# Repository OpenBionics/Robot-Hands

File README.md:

# Overview

OpenBionics is an initiative for the development of:
* open source
* affordable
* light-weight
* modular

robot hands and myoelectric prosthetic devices, that can be easily reproduced using off-the-shelf materials.

This repository contains all the necessary files, to replicate our robot hands.

For more information visit [OpenBionics.](http://www.openbionics.org/)

We have published a complete tutorial for the replication of our hands. The tutorial can be found [here.](http://www.openbionics.org/TR2015_OpenBionics_RobotHandsGuide.pdf)

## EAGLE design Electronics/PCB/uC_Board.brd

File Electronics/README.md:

# Electronics

This folder presents the electronics for the robot hands and for the interfaces (the Schematic, the PCB Layout and the OpenBionics library).
In order to control the RC or the AX12 servo motor, we use the arduino Micro Pro microcontroller platform, combined with a custom "Shield".

More information about Arduino Micro can be found [here.](http://arduino.cc/en/Main/ArduinoBoardMicro)

# Pinout
The Pin Mapping of the Arduino Micro Pro "Shield".

# Build of Materials of main PCB
	Part           Value              Device             Package 
	ARDUINO_MICRO  -                  -		     -
	C1             100u               CPOL-EUE2.5-6      E2,5-6  
	IC1            74LS241N           74LS241N           DIL20 
	J1             -                  HEADER-2X3P-2.54   -
	J2             SCREW-TERMINAL-2P  SCREW-TERMINAL-2P  -
	J3             -                  HEADER-2P-65/35MIL -          
	J4             -                  HEADER-2P-65/35MIL -    
	R1             10k                RESISTOR1206       1206
	R2             10k                RESISTOR1206       1206
	R3             10k                RESISTOR1206       1206
	S1             -                  SWITCH-SPDTSMD2    -  

# Mount PCB in to Robot Hands

You can attach the PCB at the PCBMount.STL part of the robot hands, using two M2x8 screws and two M2 nuts.

# Interfaces

#####RobotHandExtension
This interface requires push buttons and wires with the appropriate terminals.
The push buttons are placed in suitable pockets in RobotHandExtension part. Moreover, the  RobotHandExtension part has the necessary routing for the wires. The open button pin is B1 and it is placed on the top of the RobotHandExtension part. The close button pin is B2 and it is placed on the right hand side of the same part.

######Build of Materials
    2x push buttons
    2x wires terminals for HEADER-2P-65/35MIL (HEADER-2P)

#####SliderBox
This interface requires one arduino board and two linears potentiometers.
The potentiometers are connected to the analog inputs A0 and A1 of arduino board.

######Build of Materials
    2x linear potentiometer 10k (linear)
    1x Arduino board
    1x Jumper Wire Pack

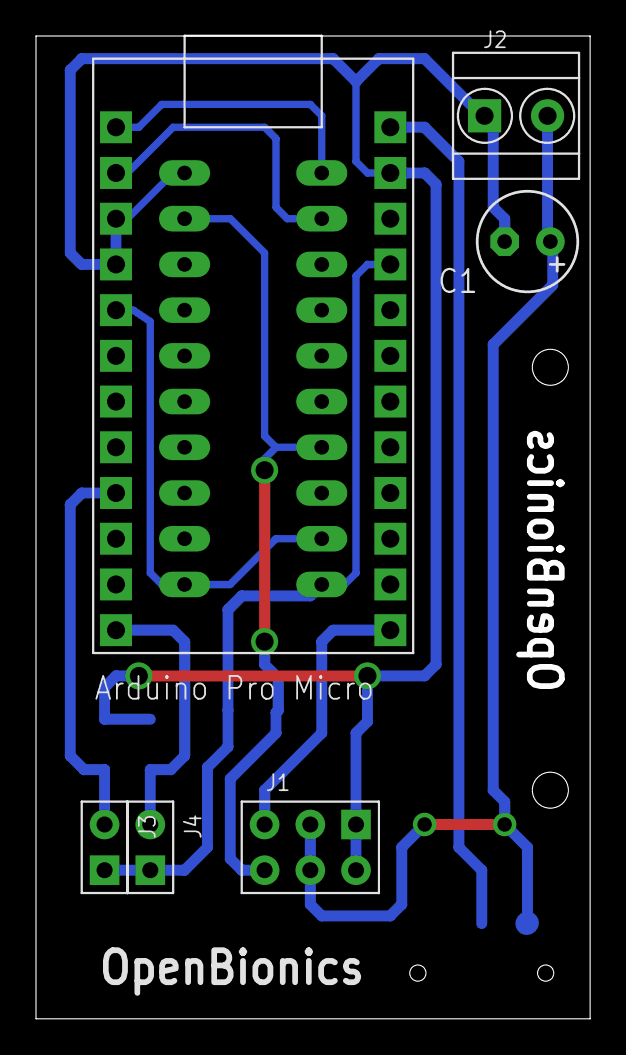
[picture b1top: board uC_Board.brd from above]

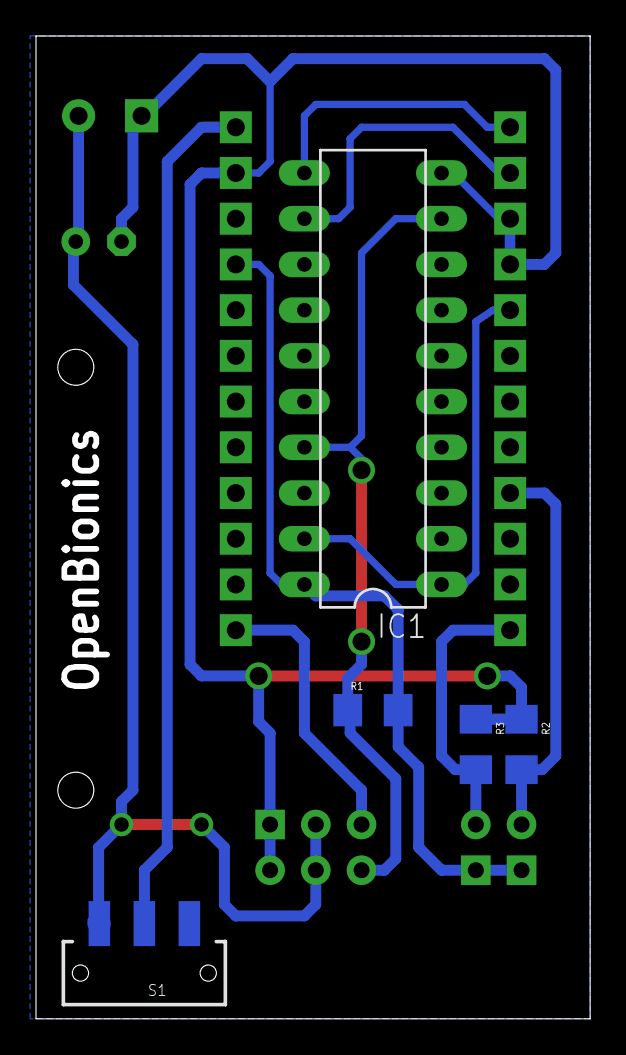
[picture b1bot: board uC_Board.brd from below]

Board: 2 copper layers, 30.8 x 54.6 mm, 11 parts (5 on the bottom side), 11 nets.

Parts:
ARDUINO_MICRO: ARDUINO_PRO_MICROARDUINO_BOARD; ARDUINO_MICRO_PRO
C1: 100u; E2,5-6
IC1: 74LS241N; DIL20
J1: 1; 2X3P-2.54-65/35MIL
J2: SCREW-TERMINAL-2P-3470070P1; 2P-3.5
J3: 2; 2P-2.54-65/35MIL
J4: 3; 2P-2.54-65/35MIL
R1, R2, R3: 10k; 1206
S1: 1; SWITCH-SPDT-SMD

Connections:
BUTTON1: ARDUINO_MICRO.9, J3.2, R2.2
BUTTON2: ARDUINO_MICRO.12, J4.2, R3.2
C_DATA: ARDUINO_MICRO.5, IC1.1, IC1.19
DATA: IC1.9, IC1.17, J1.4, R1.1
GND: ARDUINO_MICRO.3, ARDUINO_MICRO.4, ARDUINO_MICRO.23, C1.-, IC1.10, J1.1, J1.6, J2.1, R2.1, R3.1
IO1: ARDUINO_MICRO.13, J1.3
unnamed: ARDUINO_MICRO.24, S1.2
RX: ARDUINO_MICRO.2, IC1.12
TX: ARDUINO_MICRO.1, IC1.11
VCC: ARDUINO_MICRO.21, IC1.20, J3.1, J4.1, R1.2
VS: C1.+, J1.2, J1.5, J2.2, S1.3

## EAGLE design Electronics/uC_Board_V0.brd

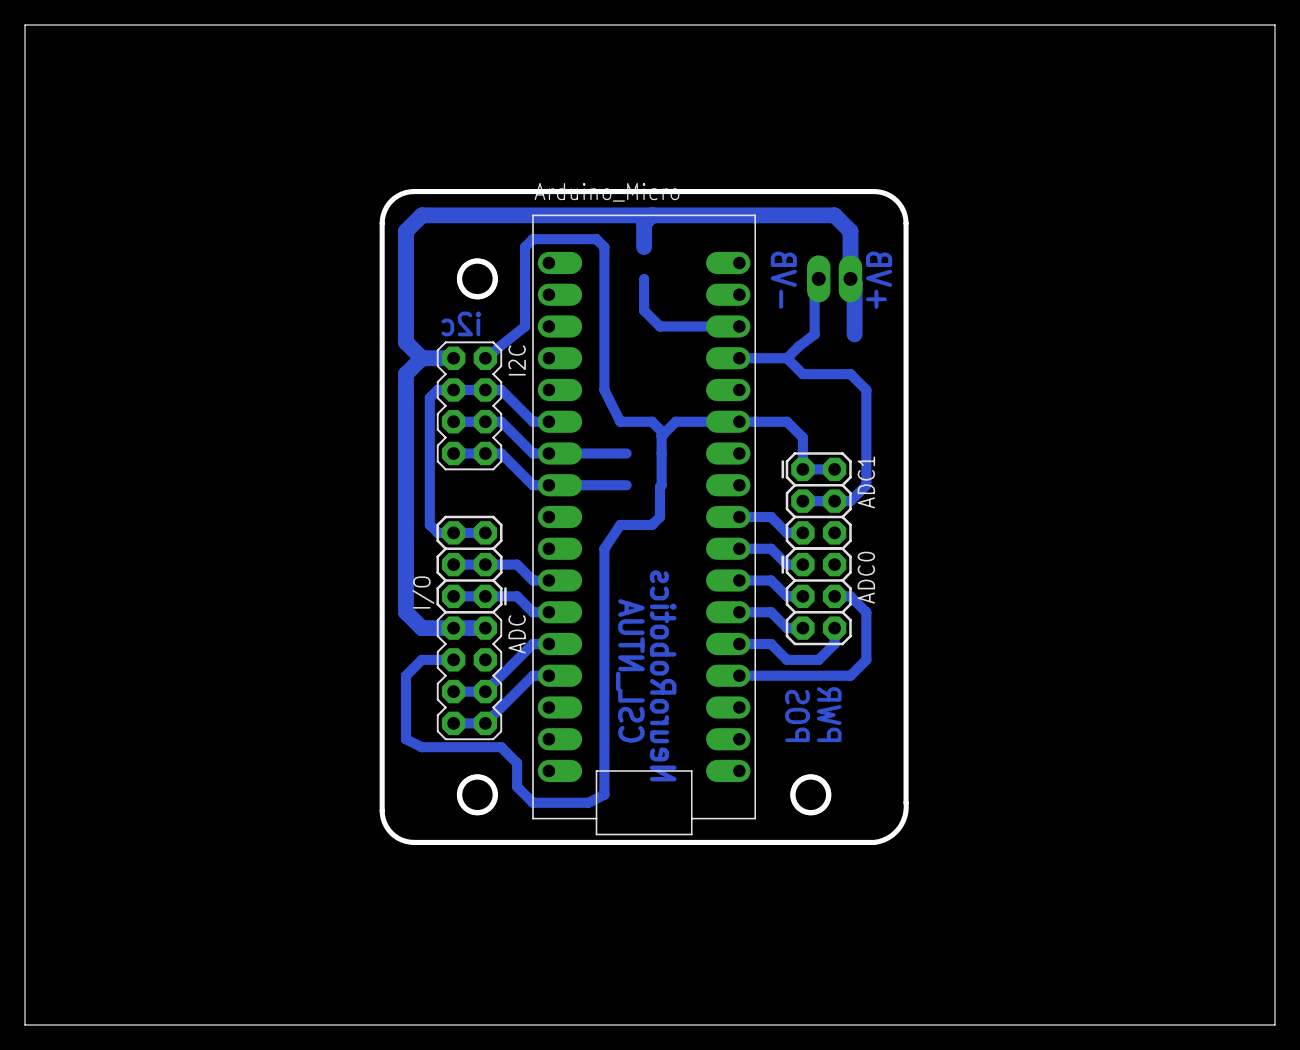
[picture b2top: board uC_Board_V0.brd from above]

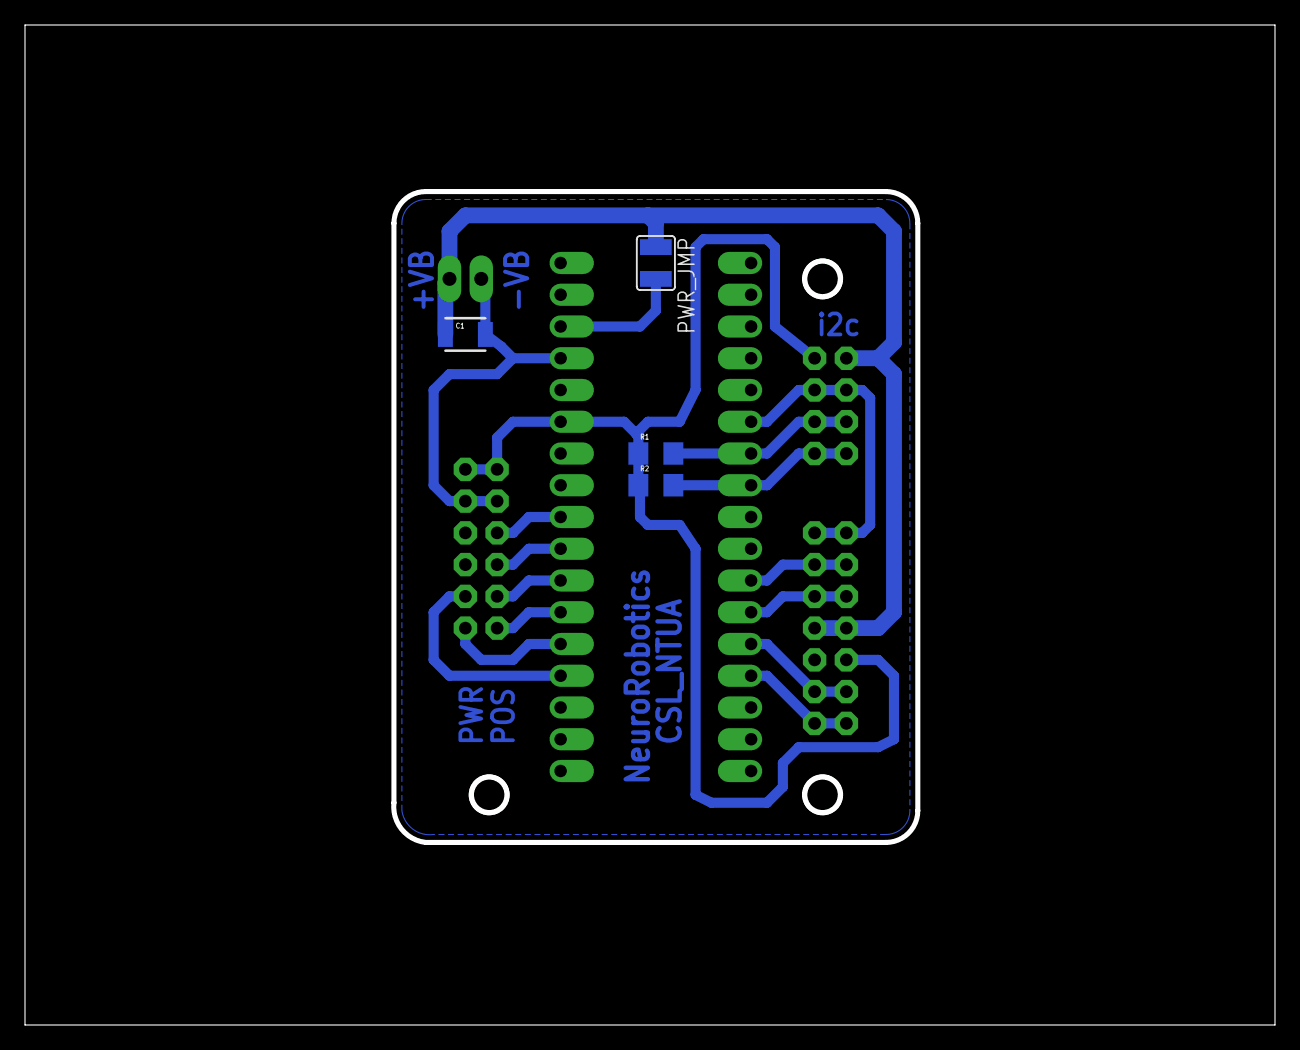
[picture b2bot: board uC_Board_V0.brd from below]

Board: 2 copper layers, 100.0 x 80.0 mm, 12 parts (4 on the bottom side), 16 nets.

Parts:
ADC: M04X2; 2X4
ADC0: 0; 2X3
ADC1: 1; 2X3
C1: 4.7u; 1210
FRAME1: FRAME-LETTER; CREATIVE_COMMONS
I2C: M04X2; 2X4
I/O: 0; 2X3
POWER: power; 1X02_LONGPADS
PWR_JMP: pwr_jmp; SJW
R1, R2: 10k; 1206
U$1: uC; ARDUINO_MICRO

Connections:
5V: ADC.3, ADC1.1, ADC1.2, I2C.2, R1.1, R2.1, U$1.29
ADC0: ADC0.4, U$1.21
ADC1: ADC0.6, U$1.22
ADC2: ADC0.5, U$1.23
ADC3: ADC0.3, U$1.24
ADC4: ADC0.1, U$1.25
ADC5: ADC1.5, U$1.26
ADC6: ADC.5, ADC.6, U$1.13
ADC7: ADC.7, ADC.8, U$1.14
GND: ADC1.3, ADC1.4, C1.2, I2C.3, I2C.4, I/O.5, I/O.6, POWER.1, U$1.6, U$1.31
I/O_0: I/O.1, I/O.2, U$1.12
PULSE: I/O.3, I/O.4, U$1.11
SCL: I2C.7, I2C.8, R2.2, U$1.8
SDA: I2C.5, I2C.6, R1.2, U$1.7
VBAT+: ADC.1, ADC.2, C1.1, I2C.1, POWER.2, PWR_JMP.1
V_IN: PWR_JMP.2, U$1.32

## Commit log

2014-02-11 second commit
2014-02-11 README commit
2014-02-11 Create pics
2014-02-11 pics
2014-02-11 README
2014-02-12 Electronics
2014-02-12 Software
2014-02-12 License
2014-02-12 Hardware
2014-02-13 CAD_Files
2014-11-16 Changed the folders name
2014-11-19 Folder structure refactoring
2014-11-19 Update README.md files.
2014-11-19 Add new PCB for RC and AX12 servo.
2014-11-19 Add new pictures for PCB.
2014-11-19 Add new CAD files for AX12 servo, PCB mount, STL for 3d-printer, to strengthen the robot base and to change the space of distal finger tip.
2014-11-23 Add gitignore in CAD Files.
2014-11-23 Add arduino code for stdServo robot hand.
2014-11-23 Add new pictures of robot hand.
2014-11-25 Update README in Software.
2014-11-25 Remove redundant folder created from auto-merging.
2014-11-25 Repair the PCB,wrong connection with Rx in AX12 servo.
2014-11-25 Add code for Dynamixel robot hand.
2014-11-25 Add code and CAD files for robot hand extension.
2014-11-25 Fix openbionics package.xml
2014-11-28 Repair the support of servoPulleyStd parts.
2014-11-28 Add correct STL file for servoPulleyStd3.STL.
2014-12-02 Add code for AX12 robot hand to control motor angle and delete unused files.
2014-12-02 Update README.md file.
2014-12-12 Update all Readme Files.
2014-12-30 Upload tutorial.
2014-12-30 Update tutorial.
2014-12-31 Update tutorial
2015-01-01 Fix README file in Electronics.
2015-01-01 Update README.md file in Overview.
2015-03-19 Repair tube plates in finger base, distal and proximal.
2015-03-20 Move TR2015_OpenBionics_RobotHandsGuide.pdf to Assembly Guide.
2015-03-20 Rename Electronics/PCB to Electronics/uC_Board.
2015-03-20 Add .gitignore to ignore Eagle backup files.
2015-03-20 Repair the Bottom Silkscreen of uC_Board PCB.
2015-03-20 Update gerber files of uC_Board PCB.
2015-03-20 Cleanup and add new designs in CAD.
2015-03-23 Add dxf files of laser cutted designs.
2015-03-23 Change the robot hand parameters to default.
2015-03-23 Update common parts, Joint1, Joint2 and tubePIP with new robot hand parameters.
2015-03-23 Add stl files of 3d printed robot hand.
2015-03-23 Add mount for kuka youbot source file and stl.
2015-03-23 Add arduino library for dynamixel motor.
2015-03-23 Add atmega32u4 (arduino micro) in marco for the selection of serial port.
2015-03-28 Add all components that we use in uC_Board.
2015-03-28 Update the Software README.md.
2015-03-28 Correction wrongs in Software/README.md.
2015-04-04 Change the position of PCB slot, because the PCB is conflicted with the screws of the bottom plate.
2015-04-04 Grew up the distance between the center of the part and the tendon hole.
2015-04-04 Change the dimensions of the two parts, change the diameter of hole for M5 screw and add M5 nut housing in female part.
2015-04-04 Remove the holes which arefasten the fingers, in order to make easiest the change of the fingers configuration.
2015-04-04 Change the design and fabrication parameters.
2015-04-04 Change the thickness of stdServoBase1 part, change the height of stdServoBase2 part and update the assembly and stl files.
2015-04-04 Update the 3d printed parts, assemblies and stl, after the changes in parts and RobotHandParameters.
2015-04-04 Update the laser cutted parts and assemblies, after the changes in RobotHandParameters.
2015-04-04 Update the Joint1-2 and tubePIP after the changes of the RobotHandParameters, reduce the length of tubeMCP.
2015-04-04 Rename the 92290A115 (screw M3L10) part.
2015-04-04 Add new common part, the screw M6 L12, which is used to couple the robot hand in PA10 robot arm.
2015-04-04 Add new common parts, the screw M5 L45 and M5 nut, which is used in flange coupling.
2015-04-04 Add new common part, screw M3 L12, which is used in the laser cutted robot finger base.
2015-04-04 Add new common parts, screws M2 L6 and L8, which are used for coupling of servo motors with the bottomplate (L8), and for the mounting of the pulley AX12 servo motor (L6).
2015-04-04 Add new common part, non marring screw M3 L20, which is used to connect hex stand off M3 L12 with hex stand off M3 L30.
2015-04-04 Add new common part, the spacer ID3 L2, which is used to connect pulley in laser cutted bottom plate.
2015-04-04 Update the readme in Couplings direcotry, after the changes and additions in Couplings.
2015-04-04 Rename FingerBasePin.SLDPRT to FingerBase.SLDPRT, change the height of the pillar, that placed in the TopPlate, to 3mm.
2015-04-04 Move the inclination to one side of JointBase, in order to print easier than before and update the stl.
2015-04-04 Add sockets in FingerDIP and FingerPIP for JointBase1-2, update the parts and stl after the changes in RobotHandParameters.
2015-04-04 Update the assemblies of the Finger.SLDASM and the RobotHand.SLDASM, after the changes and additions of the parts and the RobotHandParameters.
2015-04-10 Update LICENSE.txt, remove the non-commercial restriction that are not compatible with the open source.
2015-04-10 Update the license in assembly guide.
2015-04-16 Create gh-pages branch via GitHub
2015-05-04 Correct the wrongs in references.
2015-05-30 Move the folder CAD/Laser Cutted to CAD/RobotHand/Laser Cutted.
2015-05-30 Add new Common part ScrewM5L22 and update the rest.
2015-05-30 Move to CAD/RobotHand/3d Printed and change the pillars to 2mm.
2015-05-30 Move to CAD/RobotHand/3d Printed/Robot Finger .
2015-05-30 Move to CAD/RobotHand/3d Printed/ and add in TopPlate the holes for fingers.
2015-05-30 Move to CAD/RobotHand/3d Printed/ and update the RobotHand.SLDASM .
2015-05-30 Print the messages of topics in RobotHand node.
2015-05-30 Serial communication patch. Check the validation of PS and VL commands (MaxAngle, MaxVel). Parse the GS command correctly ("GS 12" is not correct command).
2015-05-30 Add new files for robot hand extension interface.
2015-05-30 Add new designs for SliderBox interface.
2015-05-30 Add new ROS software and firmware for SliderBox interface.
2015-05-30 Add README for interfaces.
2015-05-31 Add new picture to describe the parameters design.
2015-05-31 Small fixes in readme files.
2015-10-05 Small fixes in robot finger parts.
2015-10-05 Small fixes in common parts.
2015-10-05 Small fixes in robot hand base.
2015-10-05 Add fabrication parameters for couplings and interfaces.
2015-10-11 Add tex source files and update gitignore.
2015-10-21 Update youbot mount and add new common part.
2015-10-21 Add common parts in robot hand assembly.
2015-10-26 Add firmware for emg interface.
2015-10-26 Small fixes. Change the rospy.rate. Cahnge queue_size.
2015-10-26 Add new node for EMG read values. Add source code. Update cmakelists file.

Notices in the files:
parts and their libraries:
SparkFun-Passives: Licensing: CC v3.0 Share-Alike You are welcome to use this library for commercial purposes.
SparkFun-Aesthetics: Released under the Creative Commons Attribution Share-Alike 3.0 License
SparkFun-Aesthetics: http://creativecommons.org/licenses/by-sa/3.0
